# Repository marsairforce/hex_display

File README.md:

A 4 digit (16 bit) binary to 7-segment display.

Wanting to have some convenient module for displaying address bus contents.

# What is this and why would I want this?
If you were playing with an old retro computer type of architecture, on a breadboard, and you wanted to view the contents of like the address bus, or a data bus as a hexadecimal value.

In a simpler time when building microcontrollers using discrete CPU to simple static RAM and EEPROM devices. Back when the interconnects between teh CPU, ROM, RAM, and peripherals were the separate parallel busses, like simple 16 bit address bus, 8 bit data bus, the control bus, etc.

Now a days one would just spend $20 and get an Arduino, or $30 and get a Raspberry pi. and then connect it by USB to your laptop. And make use of the variety of widely avaialable community software. The hard work of design has been done for you.

But when working with these old parallel binary bus types of architectures, it is useful to be able to see what is going on when you are developing the hardware and the bare-metal software.

Usually you would be a monitor and debug panel with LED and switches on it. And then you have to look at the LEDs and interpret the value of these.

Photo from [astrorat.com](http://www.astrorat.com/cosmacelf/retroelf2015.html)

But if you are used to thinking in base 16 instead of binary, then having a hexadecimal display is much better. Trying to fight the process and interpret the binary LEDS is very slow, tedious, and error prone.

Only usually if you have to want a binary-to-hex display, then you have wire up your own decoder, because there does not readily exist a binary-to-hex decoder IC.

Ok, so we can think about this and design a truth table for what pins to the LED display we want to have activated depending on what binary input there is.

You want to make four of these for your 16 bit address bus and another two for your 8 bit data bus. The discrete logic components required to do this take up as much if not more breadboard space as the rest of your microcontroller circuits. And the displays are horribly spaced randomly about your breadboard and you can hardly read them now too.

I guess sometimes it is possible where you might have access to a [GAL device](https://en.wikipedia.org/wiki/Generic_array_logic), but not as likely that you would have, or can afford, the programmer for these, because you are just an enthustiac hobbyist and trying to learn something new here and only have a pile of ~~rubbish~~ retro computer parts and a breadboard to play with. That would be awesome and elegant to craft a single inexpensive DIP device as your binary to Hex digit decoder though...

But then it is still tedious and error prone to have to wire up your testing tools when you are trying to use them to test things. Because every time you wire it up you have to go through the process of testing your testing tool.

What if you just had a convenient module you could just plug into a breadboard and have it readily display the decoded bus contents. That is what this does.

Inspired by https://www.youtube.com/watch?v=o9eQ9NhFT60

# V1 Hardware
This is a 28 DIP form factor circuit board using an Atmega 164A. Because it has a lot of IO pins.

Using Atmega164A device and 4 10mm 7 segment displays.

<table>
<tr><td>
</td><td></td></tr></table>

The device was chosen because it has enough IO pins to directly drive all the segments with display multiplexing (the common anodes, using a transistor driver).

It was supposed to be a 28 pin dip format, but it is accidentally almost too wide to fit on a breadboard. Well, almost too wide. Some creative wiring under the display module on the breadboard should work.

Since we have pins for the MISO, MOSI, SCK. We can have a mode where this thing is an I2C or SPI slave and displays values on an I2C bus? That might be an intersting use. A display module. Though I would probably just use it as a clock since thats all I seem to build these days.

The schematic is set up to have the 16 address pins, an output enable pin and a latch enable pin.

So the idea is to read the input pin values. and then display value as hex, using software to multiplex the displays.

And then here it is built and getting tested.

I made a small program to just loop and count up digits to test it, so I don't have to wire up input switches.

# Programming
At first I had some learning curve to program this. I was using the Arduino IDE (instead of spending time to get avr-gcc and the tool chain to work on its own with a Makefile, becuase.. macbook here..).

The AT164A is not directly supported hardware, but there is this project for [MightyCore](https://github.com/MCUdude/MightyCore) that seems to bring the AT164 support among others to the Arduino IDE.

I tried to use the "Arduino as ISP" sketch to create an ICSP and attached it to the pings on my module. Though it would not be recognized still.  I verified the Arduino as ISP setup worked by programming an Attiny85. That led to a tangent project to learn how to build a HVSP programmer on a second arduino to rese the fuzes, because I bricked the Attiny85 by accident. And then the desire to create an all in one programmer that can handle both cases. But that fell apart when I discovered there is already a usbtiny programmer project and not wanting to lose focus on the bigger picture which was to get this damn device I built in like February (it is now late April) to program so I can just see if it even works. You know. prototyping by designing and fabricating a PCB from the get go because stupid surface mount everything, what can possibly go wrong. Oh right, everything.

So then putting some energy into to build the usbtinyisp, as maybe that would work for me instead of the Arduino as ISP thing, but feeling no budget lately, and then remembering I had a bunch of Digispark devices that have the same-ish kind of hardware that the usbtiny programmer has. So then the idea to use this as a usbtiny isp. And a few iterations with the arduino as isp and HVSP programmers to realize the USB cable I was using for it was really a 2 wire power cable and not even a USB cable at all. How many sleepless nights are we up to now anyway. At least we now have a fork on Github for the [vusbtiny](https://github.com/marsairforce/vusbtiny) project, with digispark hardware.

So getting the usbtiny programmer to work, and then learning we need to edit the avrdude.conf file to allow it to recognize the Atmega164A device. And then learning the Arduino IDE supports a `Upload using programmer` mode, so then going back to just using that. And here we are. Other than some random crazy ramblings and a somewhat arbitrary path to get here, I have uninteligently managed to use Arduino IDE with MightyCore, the updated avrdude.conf, with a usbtinyisp.

# TODO
Some ideas so far for improment:

* Lay out the board to be not as tall. It barely fits on a breadboard now. Maybe need to use slightly smaller displays. The priority at the time was to have the edges flat and narrow so two or modules could be placed side by side for a 32 bit readout. But then we forgot we can't be too tall either.

* Create a socket adapter module to fit a standard 27xx series (E)EPROM type of DIP socket, with the pin outs of these memory devices. So we can have the hex display show the contents of the address bus. The use case here is we could place this display into a socket on a motherboard of an existing retro computer, or piggy back it onto the (E)EPROM so we can see what is going on when the computer is operating.

* Design an 8 bit version. So we can see 8 bit bus things as well. Just 2 digits then.  Maybe we can use a smaller microcontroller then, like just the At328p.

* Improve the firmware. Investigate using C and avr-gcc directly. Learning more about the registers and internal details of the microcontroller. For now the delays in the visual display of numbers were thought to be "good enough". Using the internal uncalibrated oscillator of the device, so nothing timing critical going on here too.

* Investigate adding serial input option, i2c slave feature (using the USIwire, because the SDA/SCL pins for hardware TWI are also PC0..PC1, which is A8 and A9 inputs) or SPI. We have the SPI pins on PB5..PB7 for programming, but not used in normal operation.

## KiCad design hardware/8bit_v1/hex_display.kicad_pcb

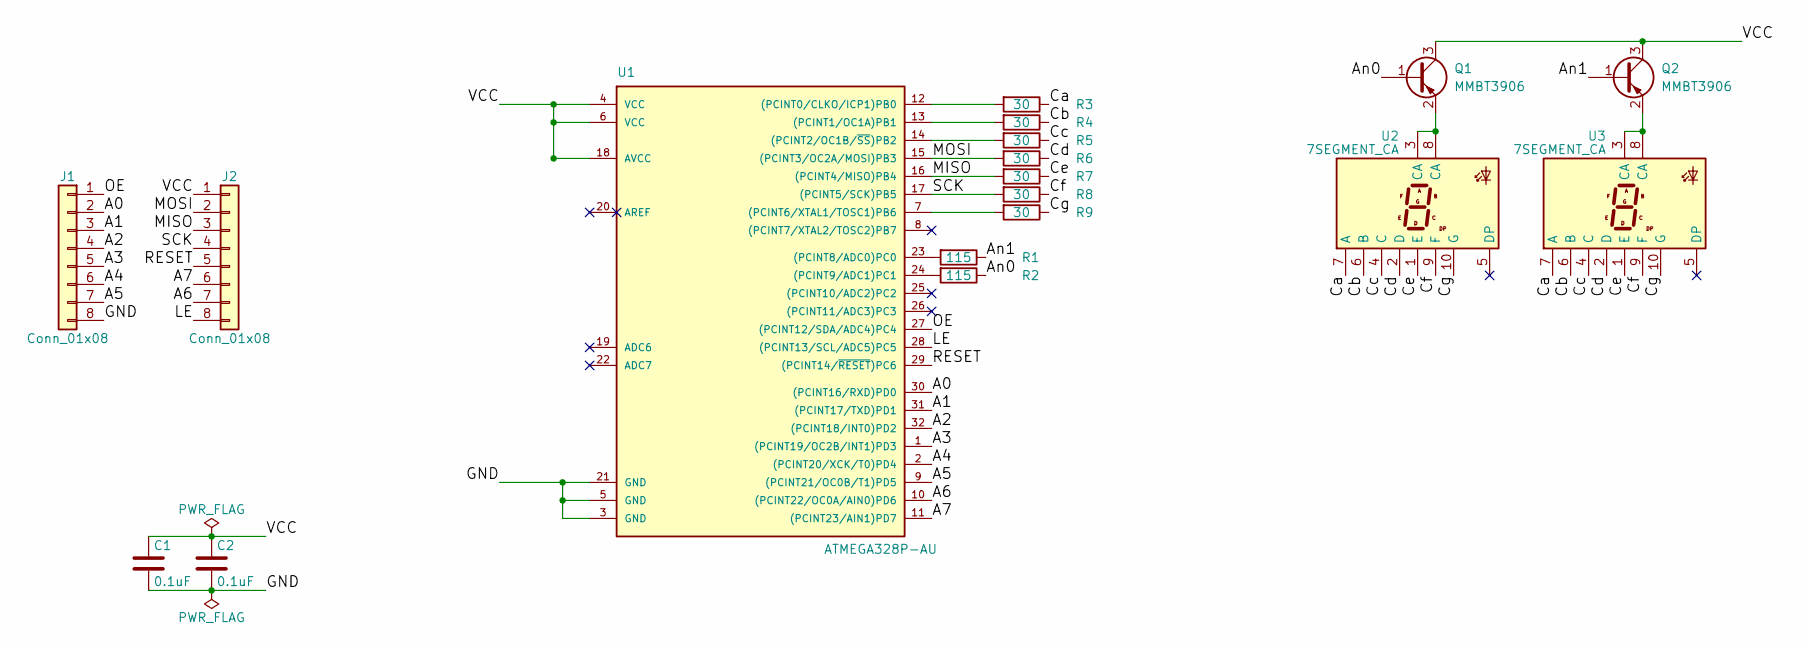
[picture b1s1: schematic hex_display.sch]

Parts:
C1, C2: 0.1uF; C_0603
J1, J2: Conn_01x08; Pin_Header_Straight_1x08_Pitch2.54mm
Q1, Q2: MMBT3906; TSOT-23
R1, R2: 115; R_0603
R3, R4, R5, R6, R7, R8, R9: 30; R_0603
U1: ATMEGA328P-AU; TQFP-32_7x7mm_Pitch0.8mm
U2, U3: 7SEGMENT_CA; VDMR10A1

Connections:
/A0: J1.2, U1.30 ((PCINT16/RXD)PD0)
/A1: J1.3, U1.31 ((PCINT17/TXD)PD1)
/A2: J1.4, U1.32 ((PCINT18/INT0)PD2)
/A3: J1.5, U1.1 ((PCINT19/OC2B/INT1)PD3)
/A4: J1.6, U1.2 ((PCINT20/XCK/T0)PD4)
/A5: J1.7, U1.9 ((PCINT21/OC0B/T1)PD5)
/A6: J2.7, U1.10 ((PCINT22/OC0A/AIN0)PD6)
/A7: J2.6, U1.11 ((PCINT23/AIN1)PD7)
/An0: Q1.1 (B), R2.1
/An1: Q2.1 (B), R1.1
/Ca: R3.1, U2.7 (A), U3.7 (A)
/Cb: R4.1, U2.6 (B), U3.6 (B)
/Cc: R5.1, U2.4 (C), U3.4 (C)
/Cd: R6.1, U2.2 (D), U3.2 (D)
/Ce: R7.1, U2.1 (E), U3.1 (E)
/Cf: R8.1, U2.9 (F), U3.9 (F)
/Cg: R9.1, U2.10 (G), U3.10 (G)
/GND: C1.2, C2.2, J1.8, U1.3 (GND), U1.5 (GND), U1.21 (GND)
/LE: J2.8, U1.28 ((PCINT13/SCL/ADC5)PC5)
/MISO: J2.3, R7.2, U1.16 ((PCINT4/MISO)PB4)
/MOSI: J2.2, R6.2, U1.15 ((PCINT3/OC2A/MOSI)PB3)
/OE: J1.1, U1.27 ((PCINT12/SDA/ADC4)PC4)
/RESET: J2.5, U1.29 ((PCINT14/~RESET~)PC6)
/SCK: J2.4, R8.2, U1.17 ((PCINT5/SCK)PB5)
/VCC: C1.1, C2.1, J2.1, Q1.3 (C), Q2.3 (C), U1.4 (VCC), U1.6 (VCC), U1.18 (AVCC)
unnamed: Q1.2 (E), U2.3 (CA), U2.8 (CA)
unnamed: Q2.2 (E), U3.3 (CA), U3.8 (CA)
unnamed: R1.2, U1.23 ((PCINT8/ADC0)PC0)
unnamed: R2.2, U1.24 ((PCINT9/ADC1)PC1)
unnamed: R3.2, U1.12 ((PCINT0/CLKO/ICP1)PB0)
unnamed: R4.2, U1.13 ((PCINT1/OC1A)PB1)
unnamed: R5.2, U1.14 ((PCINT2/OC1B/~SS~)PB2)
unnamed: R9.2, U1.7 ((PCINT6/XTAL1/TOSC1)PB6)

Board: 4 copper layers, 18 parts (0 on the bottom side), 33 nets, no tracks yet.

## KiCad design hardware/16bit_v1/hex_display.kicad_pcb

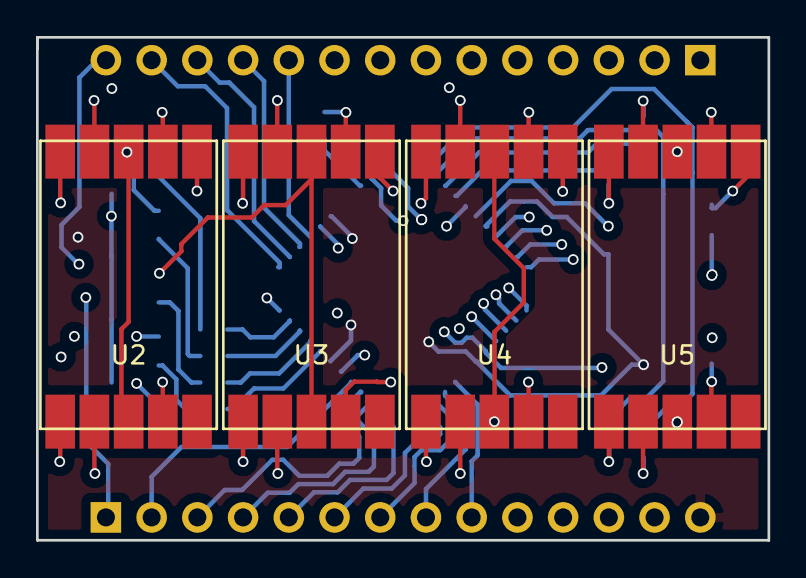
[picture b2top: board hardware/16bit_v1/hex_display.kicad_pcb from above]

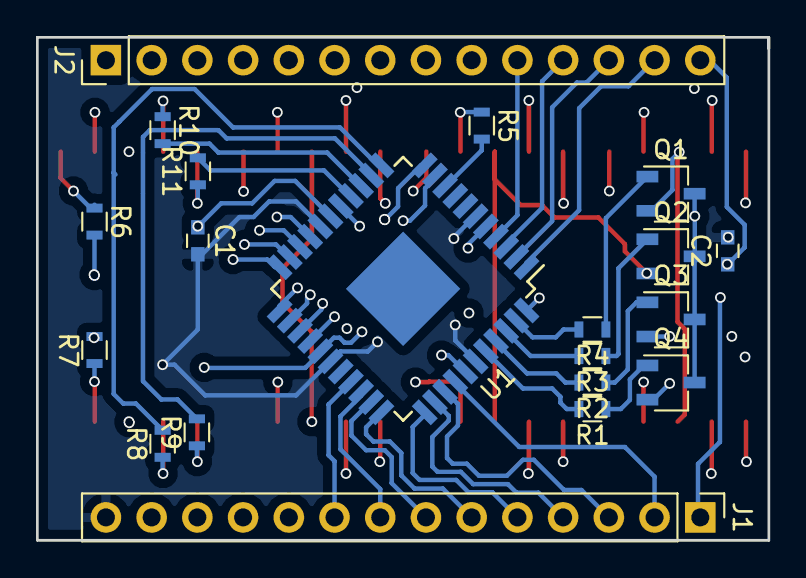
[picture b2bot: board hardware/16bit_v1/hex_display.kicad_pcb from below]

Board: 4 copper layers, 40.6 x 27.9 mm, 24 parts (20 on the bottom side), 51 nets.

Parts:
C1, C2: 0.1uF; C_0603
J1, J2: Conn_01x14; Pin_Header_Straight_1x14_Pitch2.54mm
Q1, Q2, Q3, Q4: MMBT3906; TSOT-23
R1, R2, R3, R4: 300; R_0603
R5, R6, R7, R8, R9, R10, R11: 115; R_0603
U1: ATMEGA164A-AU; TQFP-44-1EP_10x10mm_Pitch0.8mm
U2, U3, U4, U5: 7SEGMENT_CA; VDMR10A1

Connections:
/A0: J1.2, U1.37
/A1: J1.3, U1.36
/A2: J1.4, U1.35
/A3: J1.5, U1.34
/A4: J1.6, U1.33
/A5: J1.7, U1.32
/A6: J1.8, U1.31
/A7: J1.9, U1.30
/A8: J1.10, U1.19
/A9: J1.11, U1.20
/A10: J1.12, U1.21
/A11: J1.13, U1.22
/A12: J2.2, U1.23
/A13: J2.3, U1.24
/A14: J2.4, U1.25
/A15: J2.5, U1.26
/An0: Q1.1, R4.1
/An1: Q2.1, R3.1
/An2: Q3.1, R2.1
/An3: Q4.1, R1.1
/Ca: R5.1, U2.7, U3.7, U4.7, U5.7
/Cb: R6.1, U2.6, U3.6, U4.6, U5.6
/Cc: R7.1, U2.4, U3.4, U4.4, U5.4
/Cd: R8.1, U2.2, U3.2, U4.2, U5.2
/Ce: R9.1, U2.1, U3.1, U4.1, U5.1
/Cf: R10.1, U2.9, U3.9, U4.9, U5.9
/Cg: R11.1, U2.10, U3.10, U4.10, U5.10
/DVCC: J2.9, Q1.3, Q2.3, Q3.3, Q4.3
/GND: C1.2, C2.2, J1.14, U1.6, U1.18, U1.28, U1.39
/LE: J2.1, U1.16
/MISO: J2.12, U1.2
/MOSI: J2.13, U1.1
/OE: J1.1, U1.44
/RESET: J2.10, U1.4
/SCK: J2.11, U1.3
/VCC: C1.1, C2.1, J2.14, U1.5, U1.17, U1.27, U1.38
unnamed: Q1.2, U2.3, U2.8
unnamed: Q2.2, U3.3, U3.8
unnamed: Q3.2, U4.3, U4.8
unnamed: Q4.2, U5.3, U5.8
unnamed: R1.2, U1.40
unnamed: R2.2, U1.41
unnamed: R3.2, U1.42
unnamed: R4.2, U1.43
unnamed: R5.2, U1.9
unnamed: R6.2, U1.10
unnamed: R7.2, U1.11
unnamed: R8.2, U1.12
unnamed: R9.2, U1.13
unnamed: R10.2, U1.14
unnamed: R11.2, U1.15

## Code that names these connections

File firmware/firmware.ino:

/**
 * Using an Atmega 164A as a binary to hex display driver.
 * Soldered onto the circuit board with the LED digits.
 * And the need to map the IC pins to an arduino "pin" number
 * I used https://camo.githubusercontent.com/46718caeab6022a330ffed7f27109c147a16ba56/68747470733a2f2f692e696d6775722e636f6d2f735954747555492e6a7067
 * Inputs:
 * | Function | IC | Atmega | Pin | Aruino Pin reference
 * |      /OE |  1 |    PB4 |  44 |    4 |
 * |       A0 |  2 |    PA0 |  37 |   24 |
 * |       A1 |  3 |    PA1 |  36 |   25 |
 * |       A2 |  4 |    PA2 |  35 |   26 |
 * |       A3 |  5 |    PA3 |  34 |   27 |
 * |       A4 |  6 |    PA4 |  33 |   28 |
 * |       A5 |  7 |    PA5 |  32 |   29 |
 * |       A6 |  8 |    PA6 |  31 |   30 |
 * |       A7 |  9 |    PA7 |  30 |   31 |
 * |       A8 | 10 |    PC0 |  19 |   16 |
 * |       A9 | 11 |    PC1 |  20 |   17 |
 * |      A10 | 12 |    PC2 |  21 |   18 |
 * |      A11 | 13 |    PC3 |  22 |   19 |
 * |      A12 | 16 |    PC4 |  23 |   20 |
 * |      A13 | 17 |    PC5 |  24 |   21 |
 * |      A14 | 18 |    PC6 |  25 |   22 |
 * |      A15 | 19 |    PC7 |  26 |   23 |
 * |       LE | 15 |    PD7 |  16 |   15 |
 * |       NC | 20 |        |     |      |
 * |       NC | 21 |        |     |      |
 * |       NC | 22 |        |     |      |
 * |     DVCC | 23 |        |     |      |
 * |    RESET | 24 |  RESET |   4 |      |
 * |      SCK | 25 |    SCK |   3 |    7 |
 * |     MISO | 26 |   MISO |   2 |    6 |
 * |     MOSI | 27 |   MOSI |   1 |    5 |
 * |      GND | 14 |    GND | 6,18,28,39 |
 * |      VCC | 28 |    VCC | 5,17,27,38 |
 *
 *
 * Connections to LEDs:
 * | Function | Atmega | Pin | Arduino Pin Reference |
 * |       Ca |    PD0 |   9 |   8 |
 * |       Cb |    PD1 |  10 |   9 |
 * |       Cc |    PD2 |  11 |  10 |
 * |       Cd |    PD3 |  12 |  11 |
 * |       Ce |    PD4 |  13 |  12 |
 * |       Cf |    PD5 |  14 |  13 |
 * |       Cg |    PD6 |  15 |  14 |
 * |
 * |      An0 |    PB3 |  43 |   3 |
 * |      An1 |    PB2 |  42 |   2 |
 * |      An2 |    PB1 |  41 |   1 |
 * |      An3 |    PB0 |  40 |   0 |

 * Not connected: 
 * |          |  XTAL2 |   7 |
 * |          |  XTAL1 |   8 |
 * |          |   AREF |  29 |
 * 
 * Programming: 
 * Use an Arduino UNO, loaded with the "Arduino ISP sketch"
 * Then wire up as
 * | Function | Arduino | ICSP | DISPLAY | 164A |
 * |      VCC |      5V |    2 |      28 |    5 |
 * |     MOSI |      11 |    4 |      27 |    1 |
 * |     MISO |      12 |    1 |      26 |    2 |
 * |      SCK |      13 |    3 |      25 |    3 |
 * |    RESET |      10 |    5 |      24 |    4 |
 * |      GND |     GND |    6 |      14 |    6 |
 * 
 
 */

#define PIN_AN0   3
#define PIN_AN1   2
#define PIN_AN2   1
#define PIN_AN3   0

#define PIN_MOSI  5
#define PIN_MISO  6
#define  PIN_SCK   7

#define PIN_CA    8
#define PIN_CB    9
#define PIN_CC    10
#define PIN_CD    11
#define PIN_CE    12 
#define PIN_CF    13
#define PIN_CG    14

#define PIN_LE    15
#define PIN_OE    4

#define PIN_A0    24
#define PIN_A1    25
#define PIN_A2    26
#define PIN_A3    27
#define PIN_A4    28
#define PIN_A5    29
#define PIN_A6    30
#define PIN_A7    31
#define PIN_A8    16
#define PIN_A9    17
#define PIN_A10   18
#define PIN_A11   19
#define PIN_A12   20
#define PIN_A13   21
#define PIN_A14   22
#define PIN_A15   23


// bit matrix for active low cathodes to display 0..F
// where this is really just port D, segment a is LSB, segment g is bit 0x40 (mask is 0x7F)
// 0  100 0000    0x40
// 1  111 1001    0x79
// 2  010 0100    0x24
// 3  011 0000    0x30
// 4  001 1001    0x19
// 5  001 0010    0x12
// 6  000 0010    0x02
// 7  111 1000    0x78
// 8  000 0000    0x00
// 9  001 1000    0x18
// A  000 1000    0x08
// b  000 0011    0x03
// C  100 0110    0x46
// d  010 0001    0x21
// E  000 0110    0x06
// F  000 1110    0x0E

const char digits[16] = { 0x40, 0x79, 0x24, 0x30, 0x19, 0x12, 0x02, 0x78, 0x00, 0x18, 0x08, 0x03, 0x46, 0x21, 0x06, 0x0E };

void setup() {
  pinMode(PIN_AN0, OUTPUT);
  pinMode(PIN_AN1, OUTPUT);
  pinMode(PIN_AN2, OUTPUT);
  pinMode(PIN_AN3, OUTPUT);
  
  pinMode(PIN_CA, OUTPUT);
  pinMode(PIN_CB, OUTPUT);
  pinMode(PIN_CC, OUTPUT);
  pinMode(PIN_CD, OUTPUT);
  pinMode(PIN_CE, OUTPUT);
  pinMode(PIN_CF, OUTPUT);
  pinMode(PIN_CG, OUTPUT);

  pinMode(PIN_LE, INPUT_PULLUP);
  pinMode(PIN_OE, INPUT_PULLUP);

  pinMode(PIN_A0, INPUT_PULLUP);
  pinMode(PIN_A1, INPUT_PULLUP);
  pinMode(PIN_A2, INPUT_PULLUP);
  pinMode(PIN_A3, INPUT_PULLUP);
  pinMode(PIN_A4, INPUT_PULLUP);
  pinMode(PIN_A5, INPUT_PULLUP);
  pinMode(PIN_A6, INPUT_PULLUP);
  pinMode(PIN_A7, INPUT_PULLUP);
  pinMode(PIN_A8, INPUT_PULLUP);
  pinMode(PIN_A9, INPUT_PULLUP);
  pinMode(PIN_A10, INPUT_PULLUP);
  pinMode(PIN_A11, INPUT_PULLUP);
  pinMode(PIN_A12, INPUT);
  pinMode(PIN_A13, INPUT);
  pinMode(PIN_A14, INPUT);
  pinMode(PIN_A15, INPUT);

  // initially all cathodes and anodes off
  digitalWrite(PIN_CA, HIGH);
  digitalWrite(PIN_CB, HIGH);
  digitalWrite(PIN_CC, HIGH);
  digitalWrite(PIN_CD, HIGH);
  digitalWrite(PIN_CE, HIGH);
  digitalWrite(PIN_CF, HIGH);
  digitalWrite(PIN_CG, HIGH);

  digitalWrite(PIN_AN0, HIGH);
  digitalWrite(PIN_AN1, HIGH);
  digitalWrite(PIN_AN2, HIGH);
  digitalWrite(PIN_AN3, HIGH);

}

// storage for what we read from [A0..A15] inputs

int raw_value = 0;
int s = 1;

// port C is MSB, port A is LSB
void read_raw_value() {
    raw_value = (PINC << 8) | PINA;
}

void display_value() {
  PORTB &= ~0x0F;
  PORTB |= 0x07;  
  PORTD &= ~0x7F; // clear all digit bits
  PORTD |= digits[(raw_value & 0xF000) >> 12];
  delay(s);

  PORTB &= ~0x0F;
  PORTB |= 0x0B;
  PORTD &= ~0x7F; // clear all digit bits
  PORTD |= digits[(raw_value & 0x0F00) >> 8];
  delay(s);

  PORTB &= ~0x0F;
  PORTB |= 0x0D;
  PORTD &= ~0x7F; // clear all digit bits
  PORTD |= digits[(raw_value & 0x00F0) >> 4];
  delay(s);

  PORTB &= ~0x0F;
  PORTB |= 0x0E;
  PORTD &= ~0x7F; // clear all digit bits
  PORTD |= digits[(raw_value & 0x000F) ];
  delay(s );

  PORTB &= ~0x0F;
  PORTB |= 0x0F;
}

int counter = 0;
void loop() {
  if (PIND & 0x80) { // only read inputs if LE is not 0.
    read_raw_value();
  } 

  // only display things if OE is low
  if ((PINB & 0x10)) {
    display_value();
  }
//  if (counter % 200 == 0) {
//    raw_value ++;
//    counter = 0;
//  }
}

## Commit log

2018-03-04 v1 design
    board layout shipped to oshpark for processing
    https://oshpark.com/orders/PoUPhUu6
2018-03-24 assemble the board. change drive resistor to transistor. start a sketch to test the device. having problems being able to program it. not sure if this is the device, or the arduino or the macbook.
2018-05-01 change out resistor values
    during testing, noticed the displays seemed kind of dim. Experimented with values I had handy until it looked good.
2018-05-01 first attempt at firmware.
    now that i am able to actually program some software onto this thing.
2018-05-01 add the output enable and latch enable feature
2018-05-01 adding a todo section to the readme.
2018-05-01 add license
2018-05-01 add changelog file
2018-05-01 add photo
2018-05-01 typo
2018-05-01 add some context why we would build this
2018-05-01 fix images
2018-05-01 link to vusbtiny project
2018-05-05 bug fix input pull up settings
2018-05-09 move kicad files to hardware 16bit_v1 folder move firmware file to 16bit_v1 folder
2018-05-09 start an 8 bit design.
    took an attempt to lay out a PCB design. but it was a bloody mess so i deleted it out of anger because i wasted several hours trying to make it work.
